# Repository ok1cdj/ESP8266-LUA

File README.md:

ESP8266-LUA
===========

LUA scripts for ESP8266 with NodeMCU firmware

**Thermometer-DS18B20-Thingspeak** - measure temperature with DS18B20 sensor and post data to thingspeak.com

**Thermometer-DHT11-Thingspeak** - measure temperature and humidity with cheap DHT11 sensor and post data to thingspeak.com

**Thingspeak-Tweet** - example ho to send tweet using thingspeak.com API.

**Eagle-CAD** - Eagle library, currently only ESP-01, ESP-03

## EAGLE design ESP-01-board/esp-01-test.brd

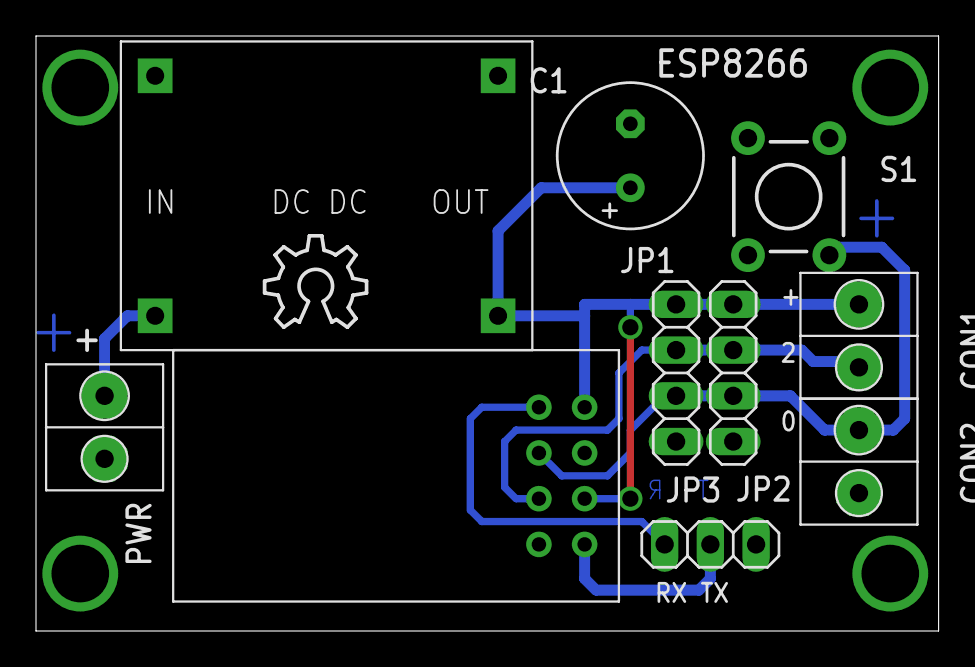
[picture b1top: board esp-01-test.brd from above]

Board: 2 copper layers, 50.1 x 33.1 mm, 11 parts (0 on the bottom side), 7 nets.

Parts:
C1: 220uF; E3,5-8
CON1, CON2: ARK550/2
JP1, JP2: 1X04
JP3: 1X03
LOGO1: OSHW_LOGO_8MILX0200-NT; OSHW_8X200_NOTEXT
PWR: ARK550/2
S1: TACTILE-PTH
U$1: ESP8266-01; ESP-01
U$2: DC-DC-SMALL; DC-DC

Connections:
GND: C1.-, CON2.2, JP1.4, JP2.1, JP3.3, PWR.2, S1.3, S1.4, U$1.P$8, U$2.P$3, U$2.P$4
unnamed: JP3.1, U$1.P$5
unnamed: JP3.2, U$1.P$1
unnamed: C1.+, CON1.1, JP1.1, JP2.4, U$1.P$2, U$1.P$4, U$2.P$2
unnamed: CON1.2, JP1.2, JP2.3, U$1.P$7
unnamed: CON2.1, JP1.3, JP2.2, S1.2, U$1.P$6
unnamed: PWR.1, U$2.P$1

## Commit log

2015-01-01 Typo error line 70 print
2015-01-02 added Eagle lbr
2015-01-11 Added Eagle files.
2015-01-11 Schematic added
2015-01-11 Removed backups
2015-01-21 Temperature value concatenation bug corrected
2015-07-12 Update dht11.lua
    Add pinouts for pins that work for all esp modules under nodemcu
